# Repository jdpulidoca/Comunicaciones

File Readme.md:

# GalPixel UniSabana GameJam 2014: The Last Hope is an A.I.???

## Historia

Bienvenido al fin de los tiempos, donde la humanidad fue dominada por los maquinas y su única salvación es una I.A.???
Juega como ANA.I. y vence al maestro y sus oleadas de enemigos, para liberar a la humanidad.

## Como Jugar 

Derrota a la oleadas de enemigos y avanza de fase.

## Controles
### Movimiento:
W: Arriba
A: Izquierda
S: Abajo
D: Derecha
### Combate
Clic Derecho: Cambio de Arma
Clic Izquierdo: Ataque

## Power Ups
 Velocidad: Aumento de Velocidad movimiento.
 Daño Cuerpo a Cuerpo: Aumento daño combate cuerpo a cuerpo.
 Daño a Distancia: Aumento daño combate a distancia.
 Velocidad de Ataque: Aumento de Velocidad ataque.
 Rango a Distancia: Aumento rango combate a distancia.
 Dash: Posibilidad de esquivar.
 Vida Máxima: Incrementa la vida del jugador.

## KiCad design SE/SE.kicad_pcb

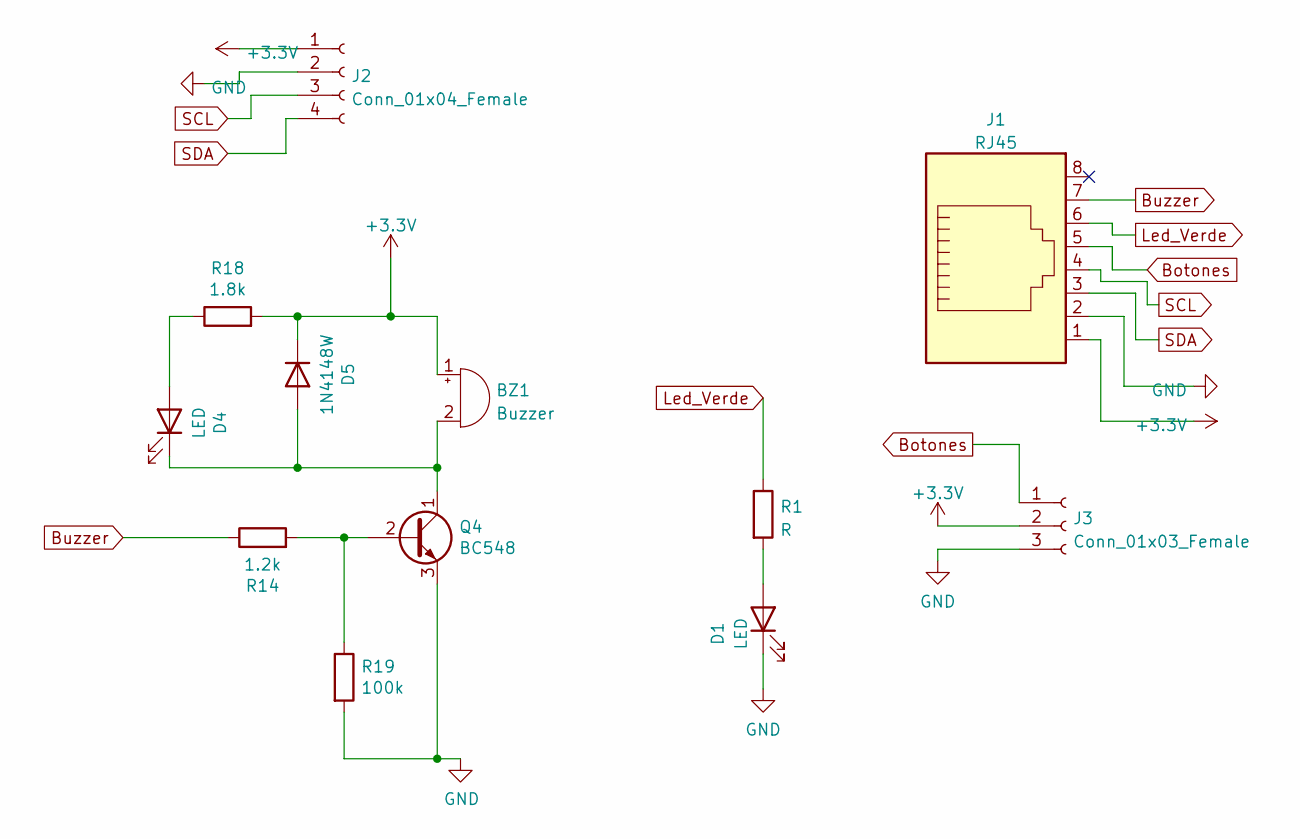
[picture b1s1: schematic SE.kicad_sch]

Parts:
BZ1: Buzzer; Buzzer_12x9.5RM7.6
D1, D4: LED; LED_D3.0mm
D5: 1N4148W; D_SOD-123
J1: RJ45; RJ45_Amphenol_54602-x08_Horizontal
J2: Conn_01x04_Female; PinSocket_1x04_P2.54mm_Vertical
J3: Conn_01x03_Female; PinSocket_1x03_P2.54mm_Horizontal
Q4: BC548; TO-92_Inline
R1: R; R_0603_1608Metric_Pad0.98x0.95mm_HandSolder
R14: 1.2k; R_0603_1608Metric_Pad0.98x0.95mm_HandSolder
R18: 1.8k; R_0603_1608Metric_Pad0.98x0.95mm_HandSolder
R19: 100k; R_0603_1608Metric_Pad0.98x0.95mm_HandSolder

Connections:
+3.3V: BZ1.1 (-), D5.1 (K), J1.1, J2.1, J3.2, R18.2
Botones: J1.5, J3.1
Buzzer: J1.7, R14.1
GND: D1.1 (K), J1.2, J2.2, J3.3, Q4.3 (E), R19.2
Led_Verde: J1.6, R1.1
unnamed: BZ1.2 (+), D4.1 (K), D5.2 (A), Q4.1 (C)
unnamed: D1.2 (A), R1.2
unnamed: D4.2 (A), R18.1
unnamed: Q4.2 (B), R14.2, R19.1
SCL: J1.4, J2.3
SDA: J1.3, J2.4

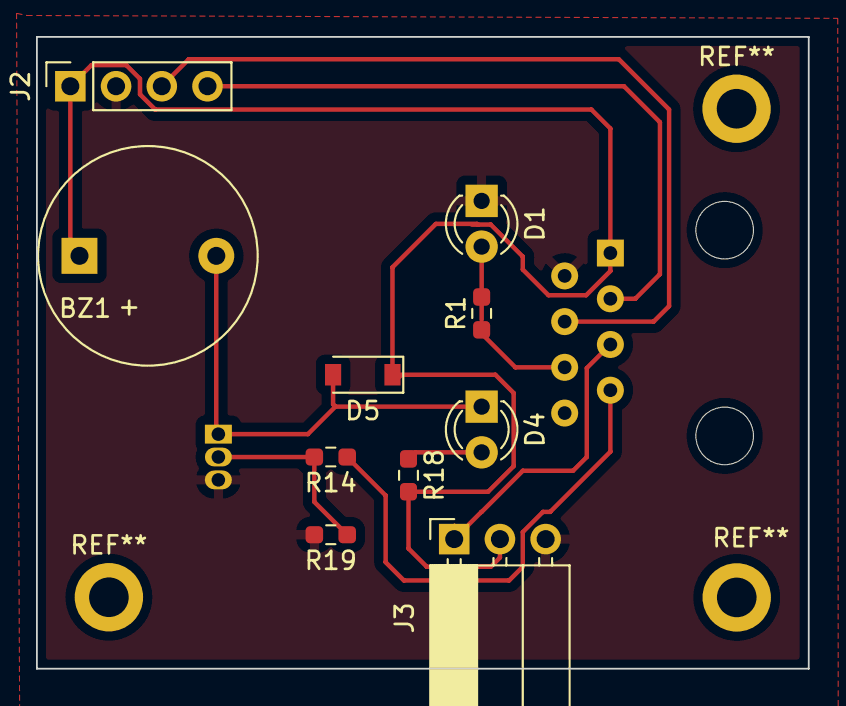
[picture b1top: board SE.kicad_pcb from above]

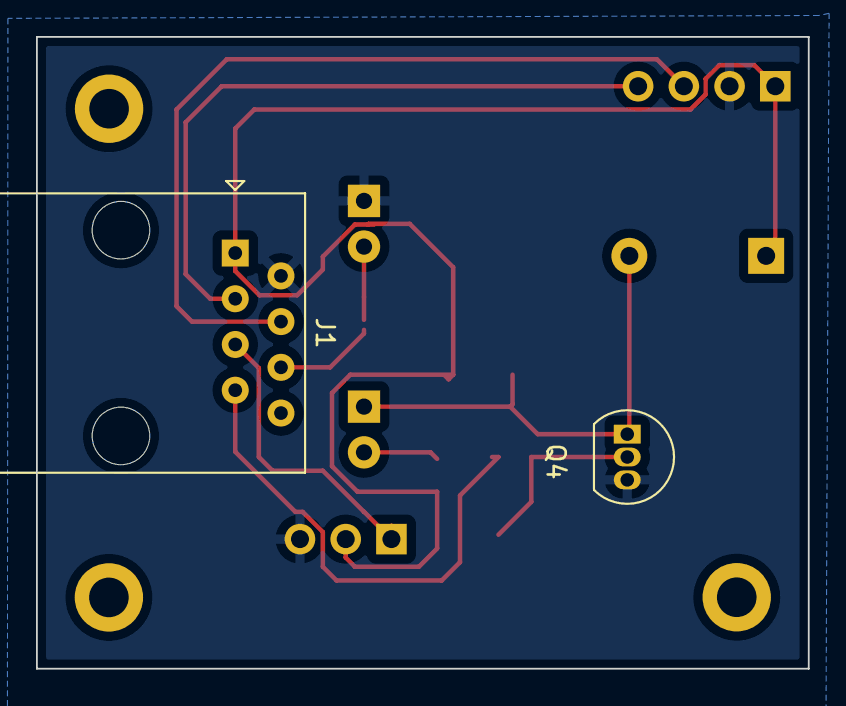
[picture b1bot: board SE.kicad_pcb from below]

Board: 2 copper layers, 42.9 x 35.1 mm, 12 parts (2 on the bottom side), 11 nets.

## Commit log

2022-10-25 Inicio Diseño caja
2022-10-25 Caja General
2022-10-25 PCB Definitiva
2022-10-25 PCB Primer Ajuste
2022-11-01 Caja, Ubicacion PCB Buzzer
2022-11-01 Caja dinal sin tornillos
2022-11-06 Comprimido Com.zip
2022-12-09 Codigo Com
